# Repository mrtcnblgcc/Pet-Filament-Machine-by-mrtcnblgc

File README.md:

# Pet-Filament-Machine-by-mrtcnblgc

Making PET filament for 3D Printer from PET bottles.

## Part List:
#### **Electronical :**
- 220V AC to 12V DC/5A power supply. 
- Arduino Pro Mini (5V, 16 Mhz).
- A4988 Step Motor Driver.
- SSD1306 OLED Display.
- 12V Heater.
- IRFZ44N Mosfet.
- 100k Ohm Thermistor.
- LM317T Voltage Regulator.
- Switch.
- Capacitors (2x4.7uF, 1x100nF).
- Resistors (1x100r, 1x330r, 5x10k, 1x1k, 1x4.7k).
- 2.54mm Male and Female Connectors.

#### **Mechanical :**
- 3D Printed parts. I'm using ecodecat3d's STL files for gear set. You can visit him/her site (https://sites.google.com/view/makeyourownecopet/inicio).
- 4x 608zz model ruller for gear set.
- Some dimensions screws and nuts.
- 3D Printer extruder set. (Heating block and nozzle) You need to expand the nozzle to 1.75mm.
- L shaped metal shelf holder for hold extruder.
- 3D Printed bottle cutter. I'm using this (https://www.thingiverse.com/thing:5442876).
- Suitable pieces of wood for the floor

## Installation 
### Mechanical Instruction
A wooden or similar base is required where you will place the gear box and heater block. First, you need to create the gear box, connect the motor to the gear box. Then, you should place the heater block in line with the gear box. I placed the power supply behind the wooden block that I used. If you want, you can place it in an independent place. You can also place the piece that we will use to cut the pet bottles on this wooden base like I did.

1.1) Placing gearbox and heater block.

1.2) Placing power supply and the piece we will use to cut the PET bottles

### Electronical Instruction
I installed the electronic card on a perforated board. However, a printed circuit board can also be produced. The schematic is as follows:

Schematic;

Creating the circuit on a perforated board;

2.1)Electronic circuit and OLED screen

2.2) Behind the circuit;

3.1) Initial menu view;

3.2) In general menu;

The right arrow button is the "OK" button. The left button is the "DOWN" button and the middle button is the "UP" button. 

To operate the heater at the desired value, press the "OK" button once while the ">" symbol is on "Set Temp". There will be no change on the screen. However, when you press the "UP" button, the value will increase by ten. Similarly, when you want to decrease, press the "DOWN" button. The value will decrease by ten. When you reach the desired value, you will return to the main menu when you press the "OK" button.

You must do the same to operate the step motor and adjust its speed. You must press the "UP" and "Down" buttons to navigate between "Set Temp" and "Set Motor" in the menu.

# Process
If you have installed mechanical and electronical things you are ready process of making filament from PET, congraculations! :)

First, you need cut the top and bottom side of the bottle. After this, you will need to make a small splinter-shaped cut on the end of the bottle to be able to insert it into the plastic bottle slicer.

And final result;

After slicing the bottle, we slice the PET thinner. Then, while the heater is cold, we pass it through the heater. 

After passing, we heat the heater between 180°C and 200°C. When the heater reaches the desired temperature, we compress the filament that comes out with a pipe-like object to the rope connected to the gear. After this process, we start the motor and let it wind. And here is our filament!

Video link; [click here](https://www.youtube.com/watch?v=tgluLH4R5xo)

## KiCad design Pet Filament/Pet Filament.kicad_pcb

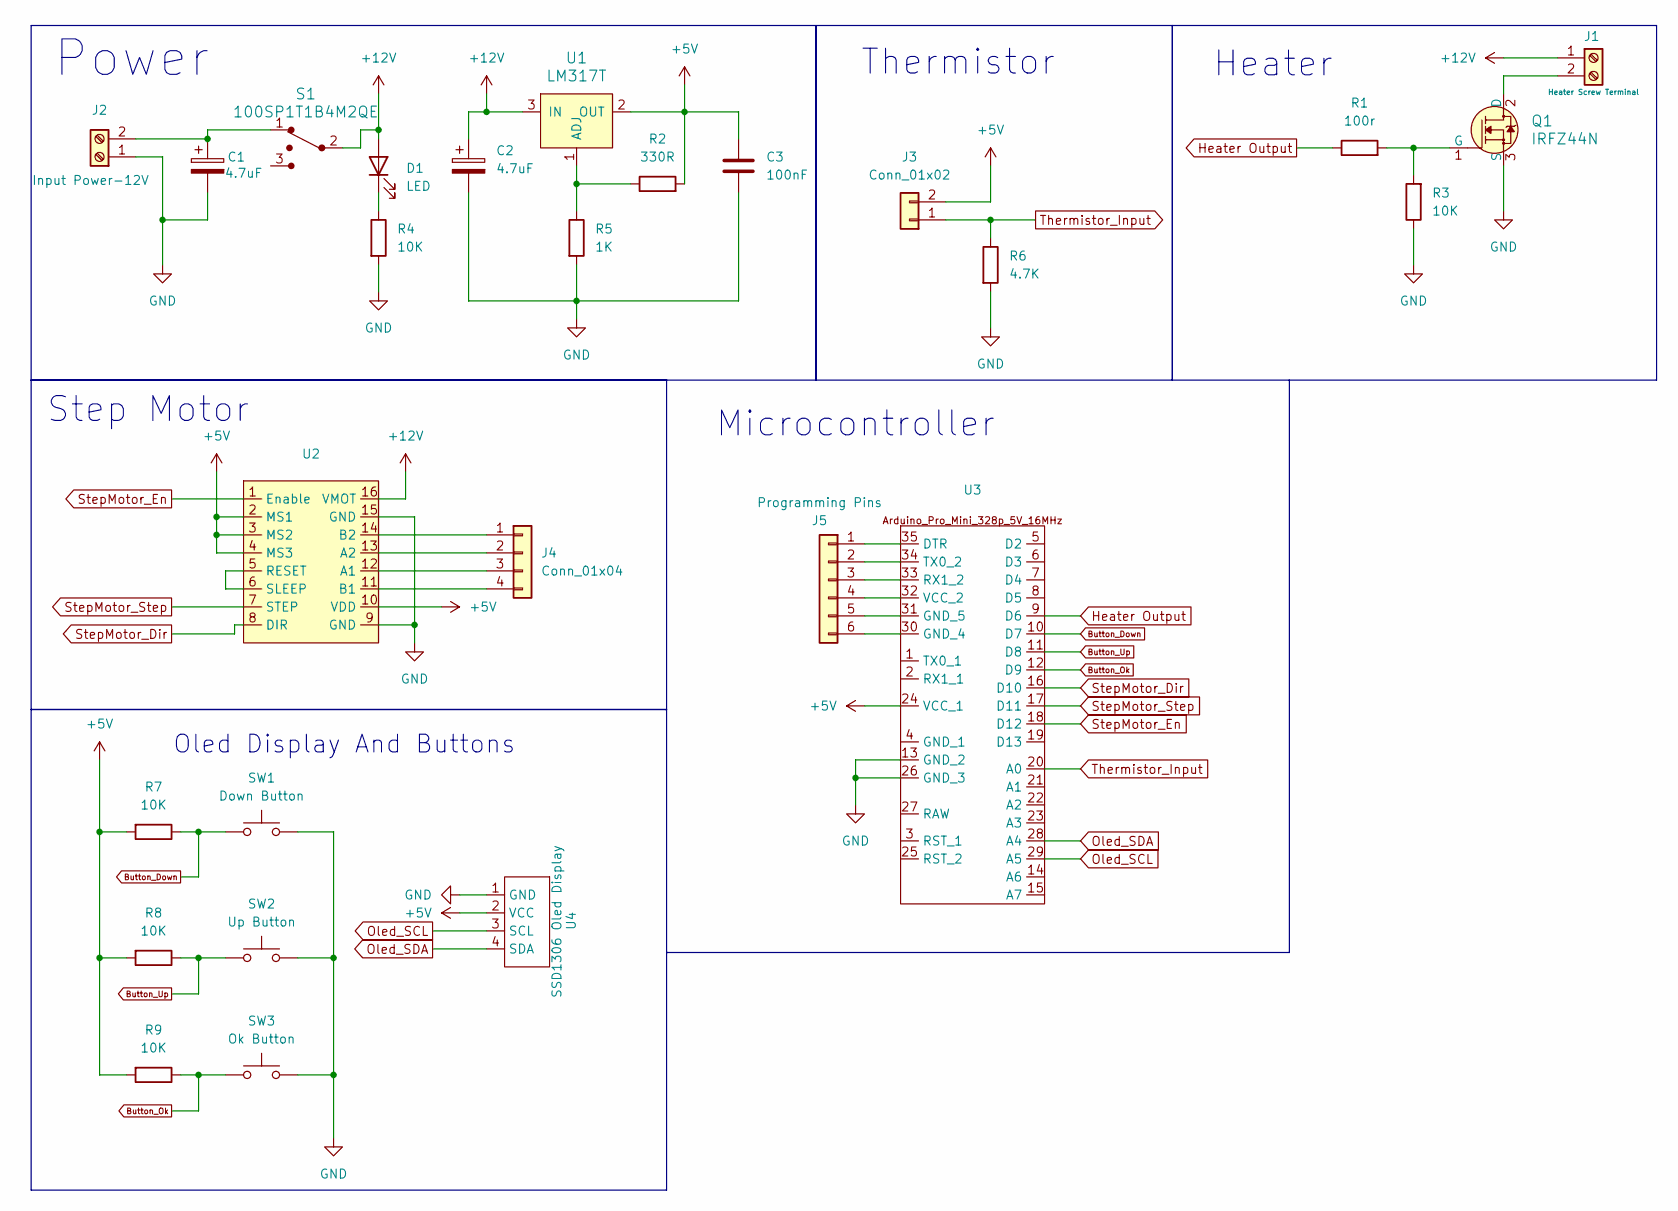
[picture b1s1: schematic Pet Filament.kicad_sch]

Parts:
C1, C2: 4.7uF; CP_Radial_D6.3mm_P2.50mm
C3: 100nF; C_Disc_D7.5mm_W2.5mm_P5.00mm
D1: LED; LED_D5.0mm_FlatTop
J1: Heater Screw Terminal; TerminalBlock_bornier-2_P5.08mm
J2: Input Power-12V; TerminalBlock_bornier-2_P5.08mm
J3: Conn_01x02; PinSocket_1x02_P2.54mm_Vertical
J4: Conn_01x04; PinHeader_1x04_P2.54mm_Vertical
J5: Programming Pins; PinSocket_1x06_P2.54mm_Vertical
Q1: IRFZ44N; TO-220-3; MPN IRF540NPBF
R1: 100r; R_Axial_DIN0207_L6.3mm_D2.5mm_P10.16mm_Horizontal
R2: 330R; R_Axial_DIN0207_L6.3mm_D2.5mm_P10.16mm_Horizontal
R3, R4, R7, R8, R9: 10K; R_Axial_DIN0207_L6.3mm_D2.5mm_P10.16mm_Horizontal
R5: 1K; R_Axial_DIN0207_L6.3mm_D2.5mm_P10.16mm_Horizontal
R6: 4.7K; R_Axial_DIN0207_L6.3mm_D2.5mm_P10.16mm_Horizontal
S1: 100SP1T1B4M2QE; Toggle_Switch_100SP1T1B4M2QE; MPN 100SP1T1B4M2QE
SW1: Down Button; SW_PUSH_6mm
SW2: Up Button; SW_PUSH_6mm
SW3: Ok Button; SW_PUSH_6mm
U1: LM317T; TO-220-3; MPN LM317T
U2: A4988_Board
U3: Arduino_Pro_Mini_5V_Board
U4: SSD1306 Oled Display; Lib-SSD1306-Oled-I2C-128x64

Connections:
+5V: C3.1, J3.2, R2.2, R7.2, R8.2, R9.2, U1.2 (OUT), U2.2 (MS1), U2.3 (MS2), U2.4 (MS3), U2.10 (VDD), U3.24 (VCC_1), U4.2 (VCC)
+12V: C2.1, D1.2 (A), J1.1, S1.2 (Com), U1.3 (IN), U2.16 (VMOT)
Button_Down: R7.1, SW1.1, U3.10 (D7)
Button_Ok: R9.1, SW3.1, U3.12 (D9)
Button_Up: R8.1, SW2.1, U3.11 (D8)
GND: C1.2, C2.2, C3.2, J2.1, Q1.3 (S), R3.1, R4.2, R5.2, R6.2, SW1.2, SW2.2, SW3.2, U2.9 (GND), U2.15 (GND), U3.13 (GND_2), U3.26 (GND_3), U4.1 (GND)
Heater Output: R1.1, U3.9 (D6)
unnamed: D1.1 (K), R4.1
unnamed: J1.2, Q1.2 (D)
unnamed: C1.1, J2.2, S1.1
unnamed: J4.1, U2.14 (B2)
unnamed: J4.2, U2.13 (A2)
unnamed: J4.3, U2.12 (A1)
unnamed: J4.4, U2.11 (B1)
unnamed: J5.1, U3.35 (DTR)
unnamed: J5.2, U3.34 (TX0_2)
unnamed: J5.3, U3.33 (RX1_2)
unnamed: J5.4, U3.32 (VCC_2)
unnamed: J5.5, U3.31 (GND_5)
unnamed: J5.6, U3.30 (GND_4)
unnamed: Q1.1 (G), R1.2, R3.2
unnamed: R2.1, R5.1, U1.1 (ADJ)
unnamed: U2.5 (RESET), U2.6 (SLEEP)
Oled_SCL: U3.29 (A5), U4.3 (SCL)
Oled_SDA: U3.28 (A4), U4.4 (SDA)
StepMotor_Dir: U2.8 (DIR), U3.16 (D10)
StepMotor_En: U2.1 (Enable), U3.18 (D12)
StepMotor_Step: U2.7 (STEP), U3.17 (D11)
Thermistor_Input: J3.1, R6.1, U3.20 (A0)

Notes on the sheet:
Heater
Power
Thermistor
Step Motor
Microcontroller
Oled Display And Buttons

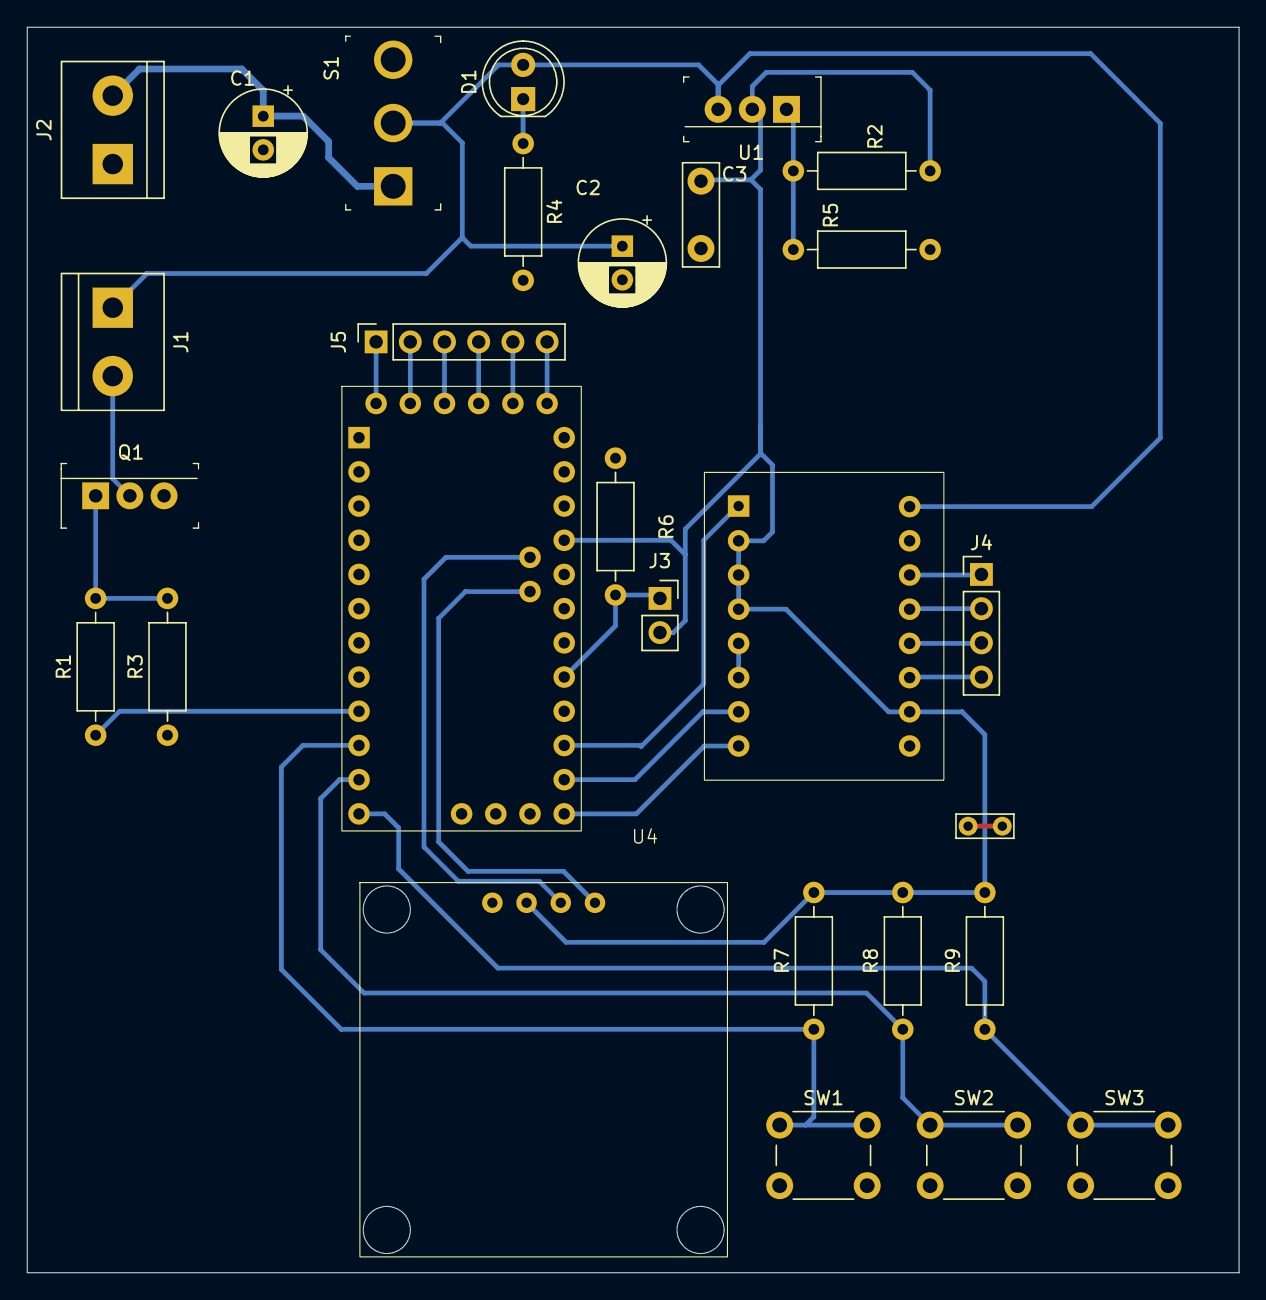
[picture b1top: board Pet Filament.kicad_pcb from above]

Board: 2 copper layers, 90.0 x 92.5 mm, 27 parts (0 on the bottom side), 29 nets.

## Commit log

2024-10-09 Rename fp-info-cache to fp-info-cache
2024-10-09 rename folder
2024-10-09 Create Photos & Videos
2024-10-09 Update and rename Photos & Videos to Photos & Videos ../asdasd
2024-10-09 Create asd
